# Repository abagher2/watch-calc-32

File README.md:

# StackCalc32 ⌚️🖩

StackCalc32 is a rebellion against slow, clunky school calculators. It completely ditches the equals sign in favor of "Stack Math" (Reverse Polish Notation)—the fastest, most efficient mental hack for solving complex math. Designed to be a world-class, rigorous tool for students, it is available as a suite of Apple ecosystem apps and as a fully open-source physical hardware device.

This monorepo contains the entire project, spanning iOS, watchOS, embedded firmware, and physical hardware designs.

## 🌟 Features

- **True Stack Math Engine**: A robust Reverse Polish Notation core (`RPNCore`) designed for precision, speed, and mathematical rigor without the mess of parentheses.
- **Cross-Platform Software**:
  - **Apple Watch App (`StackCalc32`)**: A full-featured calculator on your wrist, complete with equation plotting, statistical analysis, and complex math functions.
  - **iOS/iPadOS App (`StackCalc32-iOS`)**: A companion app featuring an immersive, haptic-enabled numpad (`HapticNumpadView`) that feels incredibly tactile—like a premium gaming device.
- **Physical Hardware**: Fully open-source 3D models and PCB designs for building your own physical StackCalc32 device. Designed to be ultra-affordable ($10-$15 retail target).
- **Embedded Firmware**: Microcontroller code powering the physical calculator.

## 🚀 The Unfair Advantage

StackCalc32 introduces several modern capabilities designed to give you a massive edge in today's high-speed engineering and math workflows:

- **RPN Equation Editor**: An intuitive editor that feels like programming, but is optimized for quick equation entry and evaluation without the overhead of full program management.
- **Equation Plotting**: Visually plot your equations directly on the screen to analyze functions, roots, and behaviors.
- **Built-in Constants**: A comprehensive library of built-in scientific constants for quick access during calculations.
- **Registers Display List**: Easily view and manage the contents of all your memory registers in a dedicated list view, rather than blindly recalling them one by one.
- **Advanced Division Operations**: Native support for division with remainders and modulus operations.
- **LFU (Least Frequently Used) Keys**: Dynamic keys that adapt to your usage, keeping the interface uncluttered while ensuring you always have access to the functions you need.

## ⌨️ Unique StackCalc32 Capabilities & Keystrokes

While the basic math and variable storage functions mirror the classic HP-32SII, StackCalc32 introduces powerful new capabilities. Here is how to use the features unique to our calculator:

### 1. RPN Equation Editor (Like Programming)
*Unlike the algebraic equation entry on the HP-32SII, StackCalc32 equations are entered as raw RPN sequences—providing the power of programming without the overhead of full program memory management.*
*Note on display formatting: The display shows the step number followed by the instruction (e.g., `3 RCL X` means step 3 is RCL X).*

*Example: Enter the equation `Y = 56 × X + 3`*

| Keystrokes | Display | Explanation |
| :--- | :--- | :--- |
| `[Blue Shift]` `[EQN]` | `EQN List` | Opens the Equation Editor list. |
| `[+]` *(New Eq)* | `LBL _` | Starts a new equation and prompts for a label. |
| `[A]` | `00 LBL A` | Assigns the equation to label A. |
| `5` `6` `[ENTER]` | `1 56` | Enters 56 into the sequence (step 1). |
| `[RCL]` `[X]` | `2 RCL X` | Recalls variable X (step 2). |
| `[×]` | `3 ×` | Multiplies 56 by X (step 3). |
| `3` `[+]` | `5 +` | Adds 3 to complete the RPN equation (steps 4 and 5). |

### 2. Equation Plotting
*Plot the equation you just entered to analyze its behavior visually.*

| Keystrokes | Display | Explanation |
| :--- | :--- | :--- |
| `[Blue Shift]` `[EQN]` | `A 56 RCL X × 3 +` | Select the equation from the list (it displays the full sequence). |
| `[Yellow Shift]` `[PLOT]` | `Plot Y(X)?` | Prompts for the independent variable to sweep (default X). |
| `[ENTER]` | `Plotting...` | Renders a high-res, pan/zoomable plot of the equation. |

### 3. Graphical Registers & Constants Lists
*Say goodbye to blindly guessing what is stored in your variables.*

| Keystrokes | Display | Explanation |
| :--- | :--- | :--- |
| `[Blue Shift]` `[REGS]` | `Registers...` | Opens a scrollable graphical list of all stored memory registers (A-Z). |
| `[Blue Shift]` `[CONST]` | `Constants...` | Opens the built-in scientific constants library for quick insertion. |

### 4. Advanced Division & Modulus
*Calculate integer division and remainders natively.*

| Keystrokes | Display | Explanation |
| :--- | :--- | :--- |
| `1` `7` `[ENTER]` `5` | `5.0000` | Pushes 17 and 5 to the stack. |
| `[Yellow Shift]` `[÷]` | `3.0000` | Integer division (`17 // 5`). |
| `[Yellow Shift]` `[MOD]` | `2.0000` | Returns the remainder (`17 % 5`). |

### 5. Dynamic LFU Keys
StackCalc32 features **Least Frequently Used (LFU)** adaptive keypads. As you use specific functions or variables, the interface gracefully adapts to surface your most-used keys, preventing you from having to dig through shift menus for your favorite operations.

## 📂 Repository Structure

To maintain a clean and organized monorepo ready for public open-source distribution, this repository strictly adheres to the following structure:

- `StackCalc32/` - The watchOS application target.
- `StackCalc32-iOS/` - The iOS/iPadOS application target (Container App).
- `RPNCore/` - The shared, core RPN mathematical engine.
- `Shared/` - Shared SwiftUI views, themes, and logic used across both Apple platforms.
- `Hardware/` - Physical calculator design files, including KiCAD schematics (`.kicad_sch`), PCB layouts (`.kicad_pcb`), OpenSCAD 3D models, and gerber files.
- `Firmware/` - Embedded Swift / C code for the physical microcontroller.
- `fastlane/` - Automated App Store screenshots, metadata, and submission scripts.
- `scratch/` - *(Git-ignored)* Directory for temporary scripts, parsed logs, exploratory testing, and raw extractions.

## 🛠️ Development & Building

### iOS & watchOS Apps

This project uses [XcodeGen](https://github.com/yonaskolb/XcodeGen) to manage the Xcode project configuration, eliminating `.pbxproj` merge conflicts.

1. Ensure XcodeGen is installed (e.g., via Homebrew): 
   ```bash
   brew install xcodegen
   ```
2. Generate the Xcode project:
   ```bash
   xcodegen generate
   ```
3. Open `StackCalc32.xcodeproj` in Xcode and select the target (`StackCalc32Container` for iOS/iPad or `StackCalc32` for Apple Watch) to build and run.

### Hardware & Firmware

- **3D Models**: Modify the `.scad` files in `Hardware/` and use the provided `generate_scad.py` script to compile the final `.stl` files for 3D printing. *(Note: To keep the repository light, `.stl` files are explicitly git-ignored).*
- **Firmware**: Built using the Apple Swift Embedded toolchain or Raspberry Pi Pico SDK. See the `Firmware/` directory for specific hardware bring-up and build instructions.

## 📄 License & Privacy

- **License**: Please refer to the [LICENSE](LICENSE) file for open-source licensing details.
- **Privacy Policy**: See the [Privacy Policy](PRIVACY_POLICY.md) for information regarding data collection (StackCalc32 does not collect or store user data).

---
*Built for the next generation of engineers who appreciate the elegance of RPN.*

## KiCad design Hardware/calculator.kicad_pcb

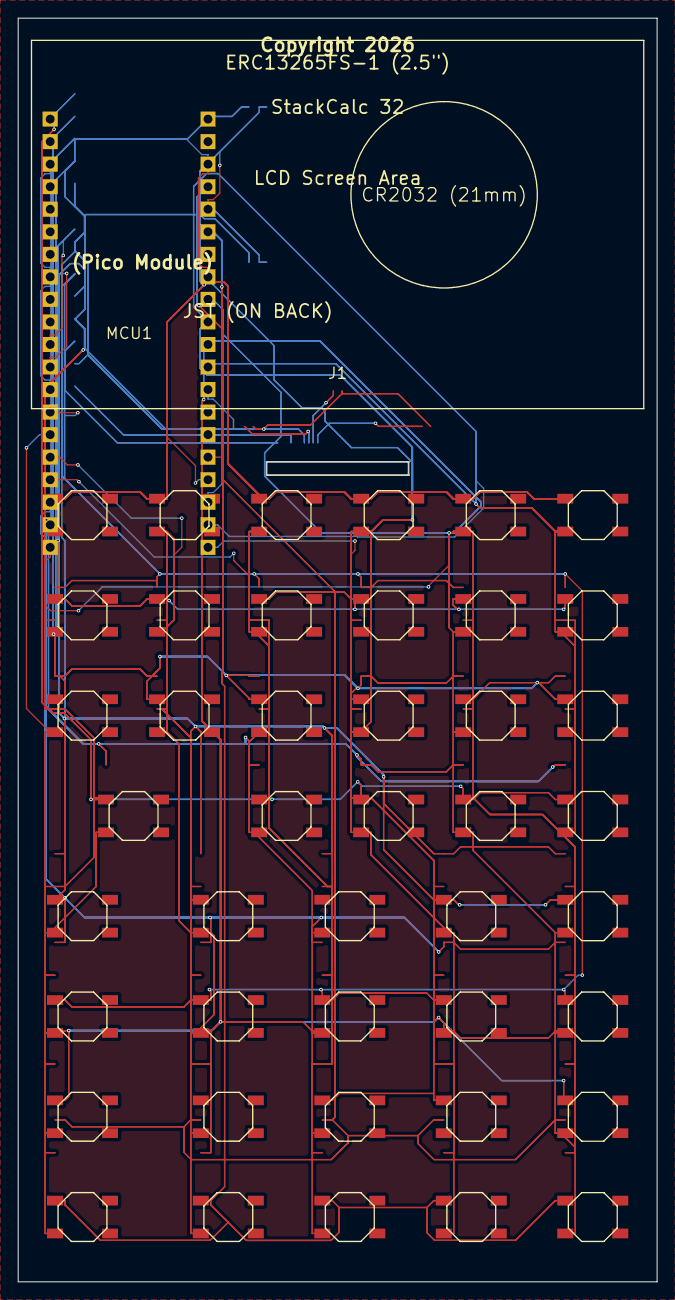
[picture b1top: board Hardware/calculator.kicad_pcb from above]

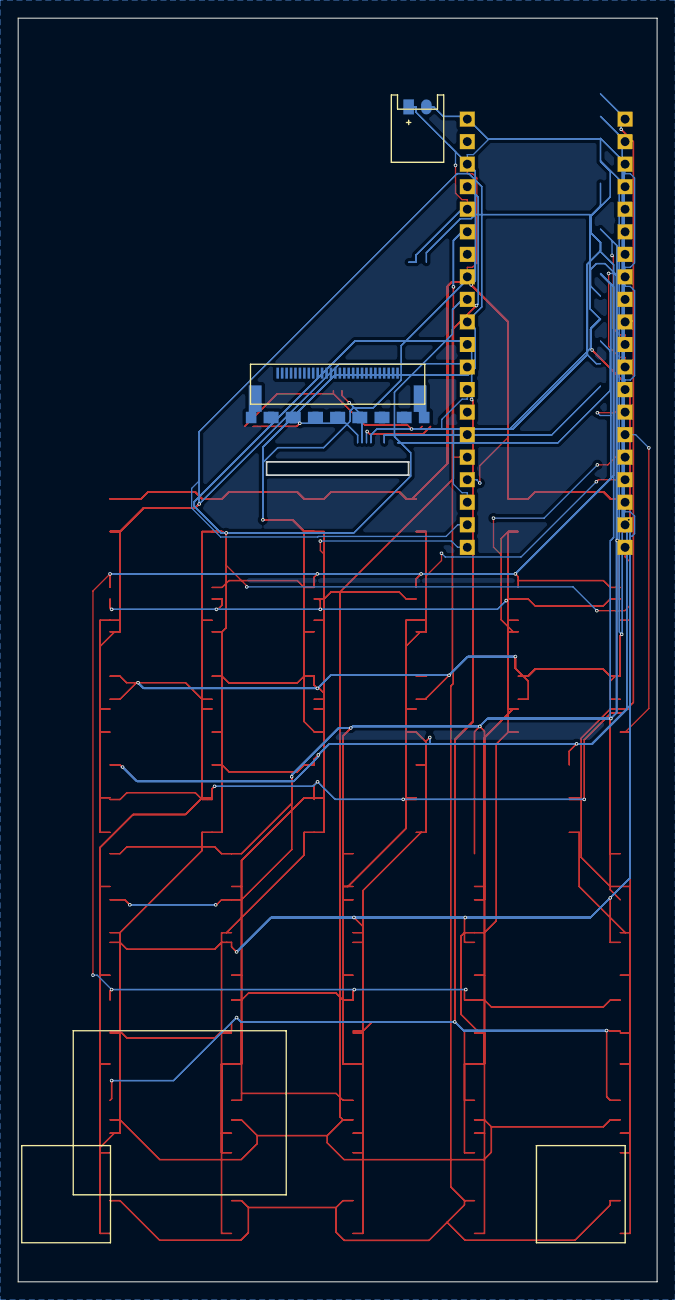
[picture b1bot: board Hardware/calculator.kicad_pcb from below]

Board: 2 copper layers, 72.0 x 142.4 mm, 54 parts (11 on the bottom side), 21 nets.

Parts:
B1, B2, B3, B4, B5, B6, B7, B8, B9, B10, B11, B12, B13, B14, B15, B16, B17, B18, B19, B20, B21, B22, B23, B24, B25, B26, B27, B28, B29, B30, B31, B32, B33, B34, B35, B36, B37: Tactile Switch 6x6mm; SW_TACT_ALPS_SKQGABE010
C1, C2, C3, C4, C5, C6, C7, C8: (no value)
J1: (no value)
JST1: JST-PH 2.0 2-Pin; JST_PH_S2B-PH-K_02x2.00mm_Angled
MCU1: (no value)
SOFT1, SOFT2, SOFT3, SOFT4, SOFT5, SOFT6: SW_TACT_ALPS_SKQGABE010

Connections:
GND: C3.2, C4.2, C5.2, C6.2, C7.2, C8.2, JST1.2, MCU1.3, MCU1.8, MCU1.13, MCU1.18, MCU1.23, MCU1.28, MCU1.33, MCU1.38
P0: B2.1, B4.1, B7.1, B10.1, B13.1, B16.1, MCU1.9
P1: B1.1, B6.1, B9.1, B12.1, B15.1, MCU1.10
P4: B3.1, B5.1, B8.1, B11.1, B14.1, B17.1, MCU1.11
P5: B18.1, B22.1, B26.1, B30.1, B34.1, MCU1.12
P6: B19.1, B23.1, B27.1, B31.1, B35.1, MCU1.14
P7: B1.2, B2.2, B3.2, B18.2, B19.2, B20.2, B21.2, MCU1.15, SOFT1.2
P8: B4.2, B5.2, B22.2, B23.2, B24.2, B25.2, MCU1.16, SOFT2.2
P9: B6.2, B7.2, B8.2, B26.2, B27.2, B28.2, B29.2, MCU1.17, SOFT3.2
P10: B20.1, B24.1, B28.1, B32.1, B36.1, MCU1.19
P14: B12.2, B13.2, B14.2, B34.2, B35.2, B36.2, B37.2, MCU1.20, SOFT5.2
P15: B9.2, B10.2, B11.2, B30.2, B31.2, B32.2, B33.2, MCU1.21, SOFT4.2
P16: B15.2, B16.2, B17.2, MCU1.22, SOFT6.2
P20: MCU1.24, SOFT1.1, SOFT2.1, SOFT3.1, SOFT4.1, SOFT5.1, SOFT6.1
P21: B21.1, B25.1, B29.1, B33.1, B37.1, MCU1.25
SPI_CS: J1.2, MCU1.2
SPI_DC: J1.4, MCU1.6
SPI_MOSI: J1.14, MCU1.5
SPI_RES: J1.3, MCU1.7
SPI_SCK: J1.13, MCU1.4
VCC: JST1.1, MCU1.36

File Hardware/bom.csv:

Designator,Value,Footprint,Description,Quantity
B24,ALPS SKQGABE010,SW_TACT_ALPS_SKQGABE010,SMD Tactile Switch for keys,1
B20,ALPS SKQGABE010,SW_TACT_ALPS_SKQGABE010,SMD Tactile Switch for keys,1
B6,ALPS SKQGABE010,SW_TACT_ALPS_SKQGABE010,SMD Tactile Switch for keys,1
B7,ALPS SKQGABE010,SW_TACT_ALPS_SKQGABE010,SMD Tactile Switch for keys,1
B29,ALPS SKQGABE010,SW_TACT_ALPS_SKQGABE010,SMD Tactile Switch for keys,1
B30,ALPS SKQGABE010,SW_TACT_ALPS_SKQGABE010,SMD Tactile Switch for keys,1
B37,ALPS SKQGABE010,SW_TACT_ALPS_SKQGABE010,SMD Tactile Switch for keys,1
B13,ALPS SKQGABE010,SW_TACT_ALPS_SKQGABE010,SMD Tactile Switch for keys,1
B14,ALPS SKQGABE010,SW_TACT_ALPS_SKQGABE010,SMD Tactile Switch for keys,1
B15,ALPS SKQGABE010,SW_TACT_ALPS_SKQGABE010,SMD Tactile Switch for keys,1
B16,ALPS SKQGABE010,SW_TACT_ALPS_SKQGABE010,SMD Tactile Switch for keys,1
B17,ALPS SKQGABE010,SW_TACT_ALPS_SKQGABE010,SMD Tactile Switch for keys,1
B19,ALPS SKQGABE010,SW_TACT_ALPS_SKQGABE010,SMD Tactile Switch for keys,1
B21,ALPS SKQGABE010,SW_TACT_ALPS_SKQGABE010,SMD Tactile Switch for keys,1
B22,ALPS SKQGABE010,SW_TACT_ALPS_SKQGABE010,SMD Tactile Switch for keys,1
B18,ALPS SKQGABE010,SW_TACT_ALPS_SKQGABE010,SMD Tactile Switch for keys,1
B23,ALPS SKQGABE010,SW_TACT_ALPS_SKQGABE010,SMD Tactile Switch for keys,1
B26,ALPS SKQGABE010,SW_TACT_ALPS_SKQGABE010,SMD Tactile Switch for keys,1
B27,ALPS SKQGABE010,SW_TACT_ALPS_SKQGABE010,SMD Tactile Switch for keys,1
B28,ALPS SKQGABE010,SW_TACT_ALPS_SKQGABE010,SMD Tactile Switch for keys,1
B32,ALPS SKQGABE010,SW_TACT_ALPS_SKQGABE010,SMD Tactile Switch for keys,1
B33,ALPS SKQGABE010,SW_TACT_ALPS_SKQGABE010,SMD Tactile Switch for keys,1
B34,ALPS SKQGABE010,SW_TACT_ALPS_SKQGABE010,SMD Tactile Switch for keys,1
B35,ALPS SKQGABE010,SW_TACT_ALPS_SKQGABE010,SMD Tactile Switch for keys,1
B36,ALPS SKQGABE010,SW_TACT_ALPS_SKQGABE010,SMD Tactile Switch for keys,1
B2,ALPS SKQGABE010,SW_TACT_ALPS_SKQGABE010,SMD Tactile Switch for keys,1
B3,ALPS SKQGABE010,SW_TACT_ALPS_SKQGABE010,SMD Tactile Switch for keys,1
B1,ALPS SKQGABE010,SW_TACT_ALPS_SKQGABE010,SMD Tactile Switch for keys,1
B4,ALPS SKQGABE010,SW_TACT_ALPS_SKQGABE010,SMD Tactile Switch for keys,1
B5,ALPS SKQGABE010,SW_TACT_ALPS_SKQGABE010,SMD Tactile Switch for keys,1
B25,ALPS SKQGABE010,SW_TACT_ALPS_SKQGABE010,SMD Tactile Switch for keys,1
B8,ALPS SKQGABE010,SW_TACT_ALPS_SKQGABE010,SMD Tactile Switch for keys,1
B9,ALPS SKQGABE010,SW_TACT_ALPS_SKQGABE010,SMD Tactile Switch for keys,1
B31,ALPS SKQGABE010,SW_TACT_ALPS_SKQGABE010,SMD Tactile Switch for keys,1
B10,ALPS SKQGABE010,SW_TACT_ALPS_SKQGABE010,SMD Tactile Switch for keys,1
B11,ALPS SKQGABE010,SW_TACT_ALPS_SKQGABE010,SMD Tactile Switch for keys,1
B12,ALPS SKQGABE010,SW_TACT_ALPS_SKQGABE010,SMD Tactile Switch for keys,1
Disp,8-Pin Female Header,Unknown,For 2.13-inch Waveshare E-Ink Module,1
SOFT2,ALPS SKQGABE010,SW_TACT_ALPS_SKQGABE010,SMD Tactile Switch for keys,1
SOFT6,ALPS SKQGABE010,SW_TACT_ALPS_SKQGABE010,SMD Tactile Switch for keys,1
SOFT4,ALPS SKQGABE010,SW_TACT_ALPS_SKQGABE010,SMD Tactile Switch for keys,1
SOFT3,ALPS SKQGABE010,SW_TACT_ALPS_SKQGABE010,SMD Tactile Switch for keys,1
SOFT1,ALPS SKQGABE010,SW_TACT_ALPS_SKQGABE010,SMD Tactile Switch for keys,1
SOFT5,ALPS SKQGABE010,SW_TACT_ALPS_SKQGABE010,SMD Tactile Switch for keys,1
JST1,JST-PH 2-Pin Male Header,JST_PH_S2B-PH-K_02x2.00mm_Angled,Battery connector for wired CR2450 holder,1
MCU1,RP2350 Pico 2,ProMicro,Raspberry Pi Pico 2 Module (or equivalent RP2350 board),1

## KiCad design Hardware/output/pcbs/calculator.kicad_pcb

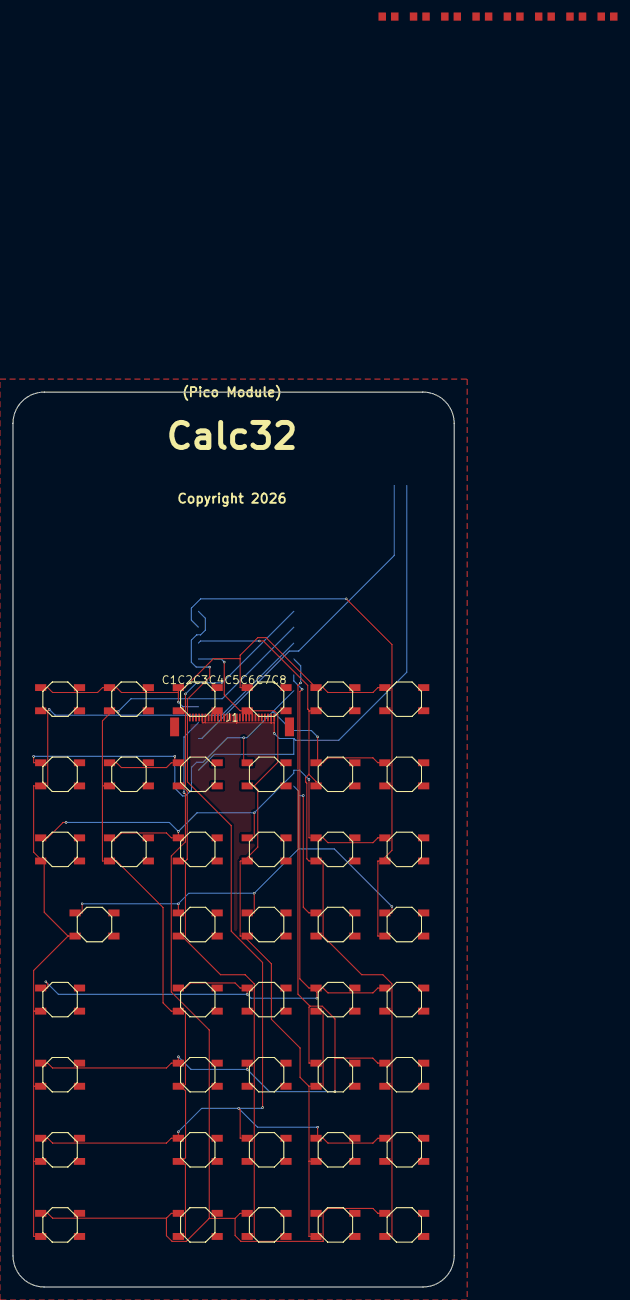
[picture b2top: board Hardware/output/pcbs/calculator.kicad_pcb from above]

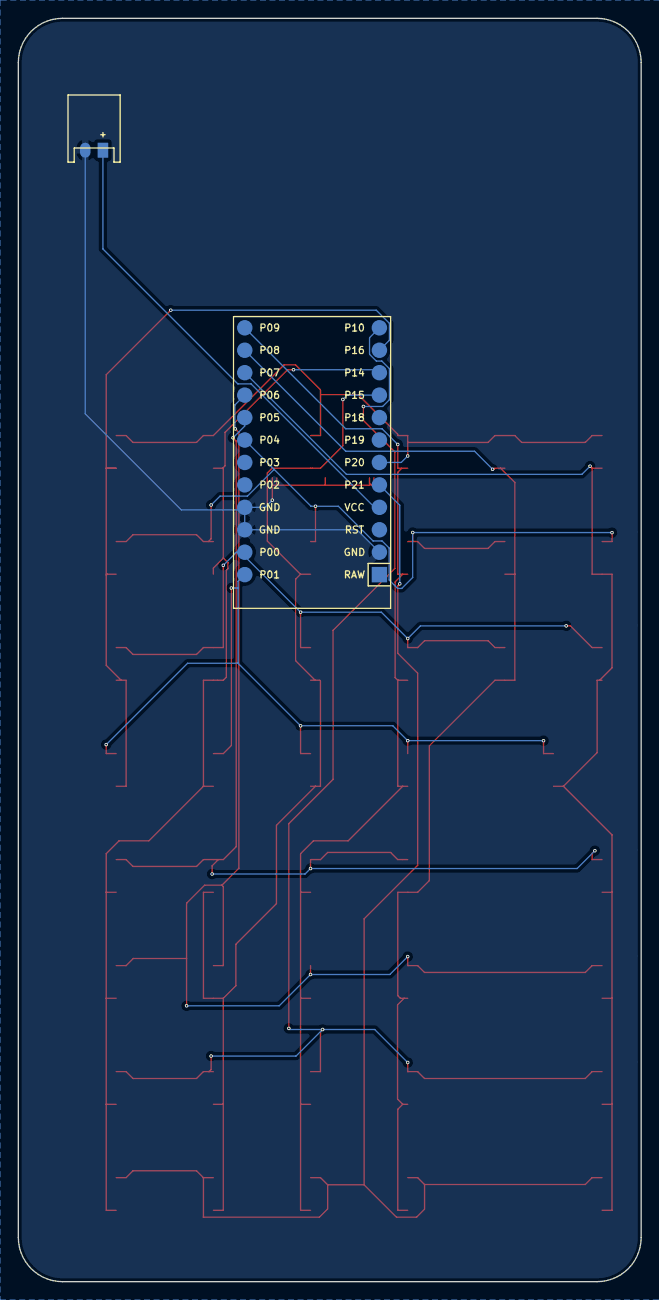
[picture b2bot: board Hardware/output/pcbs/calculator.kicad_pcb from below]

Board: 2 copper layers, 70.5 x 143.0 mm, 54 parts (2 on the bottom side), 26 nets.

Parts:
B1, B2, B3, B4, B5, B6, B7, B8, B9, B10, B11, B12, B13, B14, B15, B16, B17, B18, B19, B20, B21, B22, B23, B24, B25, B26, B27, B28, B29, B30, B31, B32, B33, B34, B35, B36, B37: SW_TACT_ALPS_SKQGABE010
C1, C2, C3, C4, C5, C6, C7, C8: (no value)
J1: Sharp_LCD
JST1: JST_PH_S2B-PH-K_02x2.00mm_Angled
MCU1: ProMicro
SOFT1, SOFT2, SOFT3, SOFT4, SOFT5, SOFT6: SW_TACT_ALPS_SKQGABE010

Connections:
GND: C3.2, C4.2, C5.2, C6.2, C7.2, C8.2, J1.5, J1.6, J1.16, J1.27, J1.28, JST1.2, MCU1.2, MCU1.15, MCU1.16
unnamed: C3.1, J1.17
unnamed: C1.1, J1.18
unnamed: C1.2, J1.19
unnamed: C2.1, J1.20
unnamed: C2.2, J1.21
unnamed: C4.1, J1.22
unnamed: C5.1, J1.23
unnamed: C6.1, J1.24
unnamed: C7.1, J1.25
unnamed: C8.1, J1.26
P0: B2.1, B4.1, B7.1, B10.1, B13.1, B16.1, MCU1.14
P1: B1.1, B6.1, B9.1, B12.1, B15.1, MCU1.13
P4: B3.1, B5.1, B8.1, B11.1, B14.1, B17.1, MCU1.19
P5: B18.1, B22.1, B26.1, B30.1, B34.1, MCU1.20
P6: B19.1, B23.1, B27.1, B31.1, B35.1, MCU1.21
P7: B1.2, B2.2, B3.2, B18.2, B19.2, B20.2, B21.2, MCU1.22, SOFT1.2
P8: B4.2, B5.2, B22.2, B23.2, B24.2, B25.2, MCU1.23, SOFT2.2
P9: B6.2, B7.2, B8.2, B26.2, B27.2, B28.2, B29.2, MCU1.24, SOFT3.2
P10: B20.1, B24.1, B28.1, B32.1, B36.1, MCU1.12
P14: B12.2, B13.2, B14.2, B34.2, B35.2, B36.2, B37.2, MCU1.10, SOFT5.2
P15: B9.2, B10.2, B11.2, B30.2, B31.2, B32.2, B33.2, MCU1.9, SOFT4.2
P16: B15.2, B16.2, B17.2, MCU1.11, SOFT6.2
P20: MCU1.6, SOFT1.1, SOFT2.1, SOFT3.1, SOFT4.1, SOFT5.1, SOFT6.1
P21: B21.1, B25.1, B29.1, B33.1, B37.1, MCU1.5
VCC: JST1.1, MCU1.4

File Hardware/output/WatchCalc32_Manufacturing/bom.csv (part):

Designator,Value,Footprint,Part Number / SKU,Description,Quantity
B32,ALPS SKQGABE010,SW_TACT_ALPS_SKQGABE010,SKQGABE010,SMD Tactile Switch for keys. **CRITICAL PCBA NOTE:** Z-height must be exactly 1.5mm off PCB surface.,1
B33,ALPS SKQGABE010,SW_TACT_ALPS_SKQGABE010,SKQGABE010,SMD Tactile Switch for keys. **CRITICAL PCBA NOTE:** Z-height must be exactly 1.5mm off PCB surface.,1
B29,ALPS SKQGABE010,SW_TACT_ALPS_SKQGABE010,SKQGABE010,SMD Tactile Switch for keys. **CRITICAL PCBA NOTE:** Z-height must be exactly 1.5mm off PCB surface.,1
B34,ALPS SKQGABE010,SW_TACT_ALPS_SKQGABE010,SKQGABE010,SMD Tactile Switch for keys. **CRITICAL PCBA NOTE:** Z-height must be exactly 1.5mm off PCB surface.,1
B37,ALPS SKQGABE010,SW_TACT_ALPS_SKQGABE010,SKQGABE010,SMD Tactile Switch for keys. **CRITICAL PCBA NOTE:** Z-height must be exactly 1.5mm off PCB surface.,1
B9,ALPS SKQGABE010,SW_TACT_ALPS_SKQGABE010,SKQGABE010,SMD Tactile Switch for keys. **CRITICAL PCBA NOTE:** Z-height must be exactly 1.5mm off PCB surface.,1
B16,ALPS SKQGABE010,SW_TACT_ALPS_SKQGABE010,SKQGABE010,SMD Tactile Switch for keys. **CRITICAL PCBA NOTE:** Z-height must be exactly 1.5mm off PCB surface.,1
B21,ALPS SKQGABE010,SW_TACT_ALPS_SKQGABE010,SKQGABE010,SMD Tactile Switch for keys. **CRITICAL PCBA NOTE:** Z-height must be exactly 1.5mm off PCB surface.,1
B2,ALPS SKQGABE010,SW_TACT_ALPS_SKQGABE010,SKQGABE010,SMD Tactile Switch for keys. **CRITICAL PCBA NOTE:** Z-height must be exactly 1.5mm off PCB surface.,1
B24,ALPS SKQGABE010,SW_TACT_ALPS_SKQGABE010,SKQGABE010,SMD Tactile Switch for keys. **CRITICAL PCBA NOTE:** Z-height must be exactly 1.5mm off PCB surface.,1
B1,ALPS SKQGABE010,SW_TACT_ALPS_SKQGABE010,SKQGABE010,SMD Tactile Switch for keys. **CRITICAL PCBA NOTE:** Z-height must be exactly 1.5mm off PCB surface.,1
B36,ALPS SKQGABE010,SW_TACT_ALPS_SKQGABE010,SKQGABE010,SMD Tactile Switch for keys. **CRITICAL PCBA NOTE:** Z-height must be exactly 1.5mm off PCB surface.,1
B22,ALPS SKQGABE010,SW_TACT_ALPS_SKQGABE010,SKQGABE010,SMD Tactile Switch for keys. **CRITICAL PCBA NOTE:** Z-height must be exactly 1.5mm off PCB surface.,1
B28,ALPS SKQGABE010,SW_TACT_ALPS_SKQGABE010,SKQGABE010,SMD Tactile Switch for keys. **CRITICAL PCBA NOTE:** Z-height must be exactly 1.5mm off PCB surface.,1
B8,ALPS SKQGABE010,SW_TACT_ALPS_SKQGABE010,SKQGABE010,SMD Tactile Switch for keys. **CRITICAL PCBA NOTE:** Z-height must be exactly 1.5mm off PCB surface.,1
B14,ALPS SKQGABE010,SW_TACT_ALPS_SKQGABE010,SKQGABE010,SMD Tactile Switch for keys. **CRITICAL PCBA NOTE:** Z-height must be exactly 1.5mm off PCB surface.,1
B17,ALPS SKQGABE010,SW_TACT_ALPS_SKQGABE010,SKQGABE010,SMD Tactile Switch for keys. **CRITICAL PCBA NOTE:** Z-height must be exactly 1.5mm off PCB surface.,1
B4,ALPS SKQGABE010,SW_TACT_ALPS_SKQGABE010,SKQGABE010,SMD Tactile Switch for keys. **CRITICAL PCBA NOTE:** Z-height must be exactly 1.5mm off PCB surface.,1
B3,ALPS SKQGABE010,SW_TACT_ALPS_SKQGABE010,SKQGABE010,SMD Tactile Switch for keys. **CRITICAL PCBA NOTE:** Z-height must be exactly 1.5mm off PCB surface.,1
B11,ALPS SKQGABE010,SW_TACT_ALPS_SKQGABE010,SKQGABE010,SMD Tactile Switch for keys. **CRITICAL PCBA NOTE:** Z-height must be exactly 1.5mm off PCB surface.,1
B20,ALPS SKQGABE010,SW_TACT_ALPS_SKQGABE010,SKQGABE010,SMD Tactile Switch for keys. **CRITICAL PCBA NOTE:** Z-height must be exactly 1.5mm off PCB surface.,1
B7,ALPS SKQGABE010,SW_TACT_ALPS_SKQGABE010,SKQGABE010,SMD Tactile Switch for keys. **CRITICAL PCBA NOTE:** Z-height must be exactly 1.5mm off PCB surface.,1
B25,ALPS SKQGABE010,SW_TACT_ALPS_SKQGABE010,SKQGABE010,SMD Tactile Switch for keys. **CRITICAL PCBA NOTE:** Z-height must be exactly 1.5mm off PCB surface.,1
B12,ALPS SKQGABE010,SW_TACT_ALPS_SKQGABE010,SKQGABE010,SMD Tactile Switch for keys. **CRITICAL PCBA NOTE:** Z-height must be exactly 1.5mm off PCB surface.,1
B27,ALPS SKQGABE010,SW_TACT_ALPS_SKQGABE010,SKQGABE010,SMD Tactile Switch for keys. **CRITICAL PCBA NOTE:** Z-height must be exactly 1.5mm off PCB surface.,1
B31,ALPS SKQGABE010,SW_TACT_ALPS_SKQGABE010,SKQGABE010,SMD Tactile Switch for keys. **CRITICAL PCBA NOTE:** Z-height must be exactly 1.5mm off PCB surface.,1
B10,ALPS SKQGABE010,SW_TACT_ALPS_SKQGABE010,SKQGABE010,SMD Tactile Switch for keys. **CRITICAL PCBA NOTE:** Z-height must be exactly 1.5mm off PCB surface.,1
B30,ALPS SKQGABE010,SW_TACT_ALPS_SKQGABE010,SKQGABE010,SMD Tactile Switch for keys. **CRITICAL PCBA NOTE:** Z-height must be exactly 1.5mm off PCB surface.,1
B19,ALPS SKQGABE010,SW_TACT_ALPS_SKQGABE010,SKQGABE010,SMD Tactile Switch for keys. **CRITICAL PCBA NOTE:** Z-height must be exactly 1.5mm off PCB surface.,1
B26,ALPS SKQGABE010,SW_TACT_ALPS_SKQGABE010,SKQGABE010,SMD Tactile Switch for keys. **CRITICAL PCBA NOTE:** Z-height must be exactly 1.5mm off PCB surface.,1
B18,ALPS SKQGABE010,SW_TACT_ALPS_SKQGABE010,SKQGABE010,SMD Tactile Switch for keys. **CRITICAL PCBA NOTE:** Z-height must be exactly 1.5mm off PCB surface.,1
B23,ALPS SKQGABE010,SW_TACT_ALPS_SKQGABE010,SKQGABE010,SMD Tactile Switch for keys. **CRITICAL PCBA NOTE:** Z-height must be exactly 1.5mm off PCB surface.,1
B5,ALPS SKQGABE010,SW_TACT_ALPS_SKQGABE010,SKQGABE010,SMD Tactile Switch for keys. **CRITICAL PCBA NOTE:** Z-height must be exactly 1.5mm off PCB surface.,1
B15,ALPS SKQGABE010,SW_TACT_ALPS_SKQGABE010,SKQGABE010,SMD Tactile Switch for keys. **CRITICAL PCBA NOTE:** Z-height must be exactly 1.5mm off PCB surface.,1
B13,ALPS SKQGABE010,SW_TACT_ALPS_SKQGABE010,SKQGABE010,SMD Tactile Switch for keys. **CRITICAL PCBA NOTE:** Z-height must be exactly 1.5mm off PCB surface.,1
B35,ALPS SKQGABE010,SW_TACT_ALPS_SKQGABE010,SKQGABE010,SMD Tactile Switch for keys. **CRITICAL PCBA NOTE:** Z-height must be exactly 1.5mm off PCB surface.,1
B6,ALPS SKQGABE010,SW_TACT_ALPS_SKQGABE010,SKQGABE010,SMD Tactile Switch for keys. **CRITICAL PCBA NOTE:** Z-height must be exactly 1.5mm off PCB surface.,1
SOFT2,ALPS SKQGABE010,SW_TACT_ALPS_SKQGABE010,SKQGABE010,SMD Tactile Switch for keys. **CRITICAL PCBA NOTE:** Z-height must be exactly 1.5mm off PCB surface.,1
SOFT6,ALPS SKQGABE010,SW_TACT_ALPS_SKQGABE010,SKQGABE010,SMD Tactile Switch for keys. **CRITICAL PCBA NOTE:** Z-height must be exactly 1.5mm off PCB surface.,1
SOFT4,ALPS SKQGABE010,SW_TACT_ALPS_SKQGABE010,SKQGABE010,SMD Tactile Switch for keys. **CRITICAL PCBA NOTE:** Z-height must be exactly 1.5mm off PCB surface.,1
SOFT3,ALPS SKQGABE010,SW_TACT_ALPS_SKQGABE010,SKQGABE010,SMD Tactile Switch for keys. **CRITICAL PCBA NOTE:** Z-height must be exactly 1.5mm off PCB surface.,1
SOFT1,ALPS SKQGABE010,SW_TACT_ALPS_SKQGABE010,SKQGABE010,SMD Tactile Switch for keys. **CRITICAL PCBA NOTE:** Z-height must be exactly 1.5mm off PCB surface.,1
SOFT5,ALPS SKQGABE010,SW_TACT_ALPS_SKQGABE010,SKQGABE010,SMD Tactile Switch for keys. **CRITICAL PCBA NOTE:** Z-height must be exactly 1.5mm off PCB surface.,1
C1,1uF 10V X5R,Unknown,CL05A105KQ5NNNC,0402 LCD charge pump / decoupling capacitor,1
JST1,JST PH 2-pin side-entry header,JST_PH_S2B-PH-K_02x2.00mm_Angled,S2B-PH-K-S(LF)(SN),"Battery connector for wired CR2450 battery; 2.00mm pitch, side entry",1
C8,1uF 10V X5R,Unknown,CL05A105KQ5NNNC,0402 LCD charge pump / decoupling capacitor,1
C7,1uF 10V X5R,Unknown,CL05A105KQ5NNNC,0402 LCD charge pump / decoupling capacitor,1
C6,1uF 10V X5R,Unknown,CL05A105KQ5NNNC,0402 LCD charge pump / decoupling capacitor,1
C2,1uF 10V X5R,Unknown,CL05A105KQ5NNNC,0402 LCD charge pump / decoupling capacitor,1
MCU1,RP2350 Pico 2,Unknown,SC1632,"Raspberry Pi Pico 2 (non-wireless, RP2350 with dual Arm Cortex-M33 cores and FPU)",1
C5,1uF 10V X5R,Unknown,CL05A105KQ5NNNC,0402 LCD charge pump / decoupling capacitor,1
C4,1uF 10V X5R,Unknown,CL05A105KQ5NNNC,0402 LCD charge pump / decoupling capacitor,1
C3,1uF 10V X5R,Unknown,CL05A105KQ5NNNC,0402 LCD charge pump / decoupling capacitor,1
J1,10-pin 0.5mm FPC Connector,Unknown,FH12-10S-0.5SH(55),Bottom-contact ZIF FPC connector for LCD. (Placed at J1),1
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

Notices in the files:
Hardware/calculator.kicad_pcb:
Copyright 2026
